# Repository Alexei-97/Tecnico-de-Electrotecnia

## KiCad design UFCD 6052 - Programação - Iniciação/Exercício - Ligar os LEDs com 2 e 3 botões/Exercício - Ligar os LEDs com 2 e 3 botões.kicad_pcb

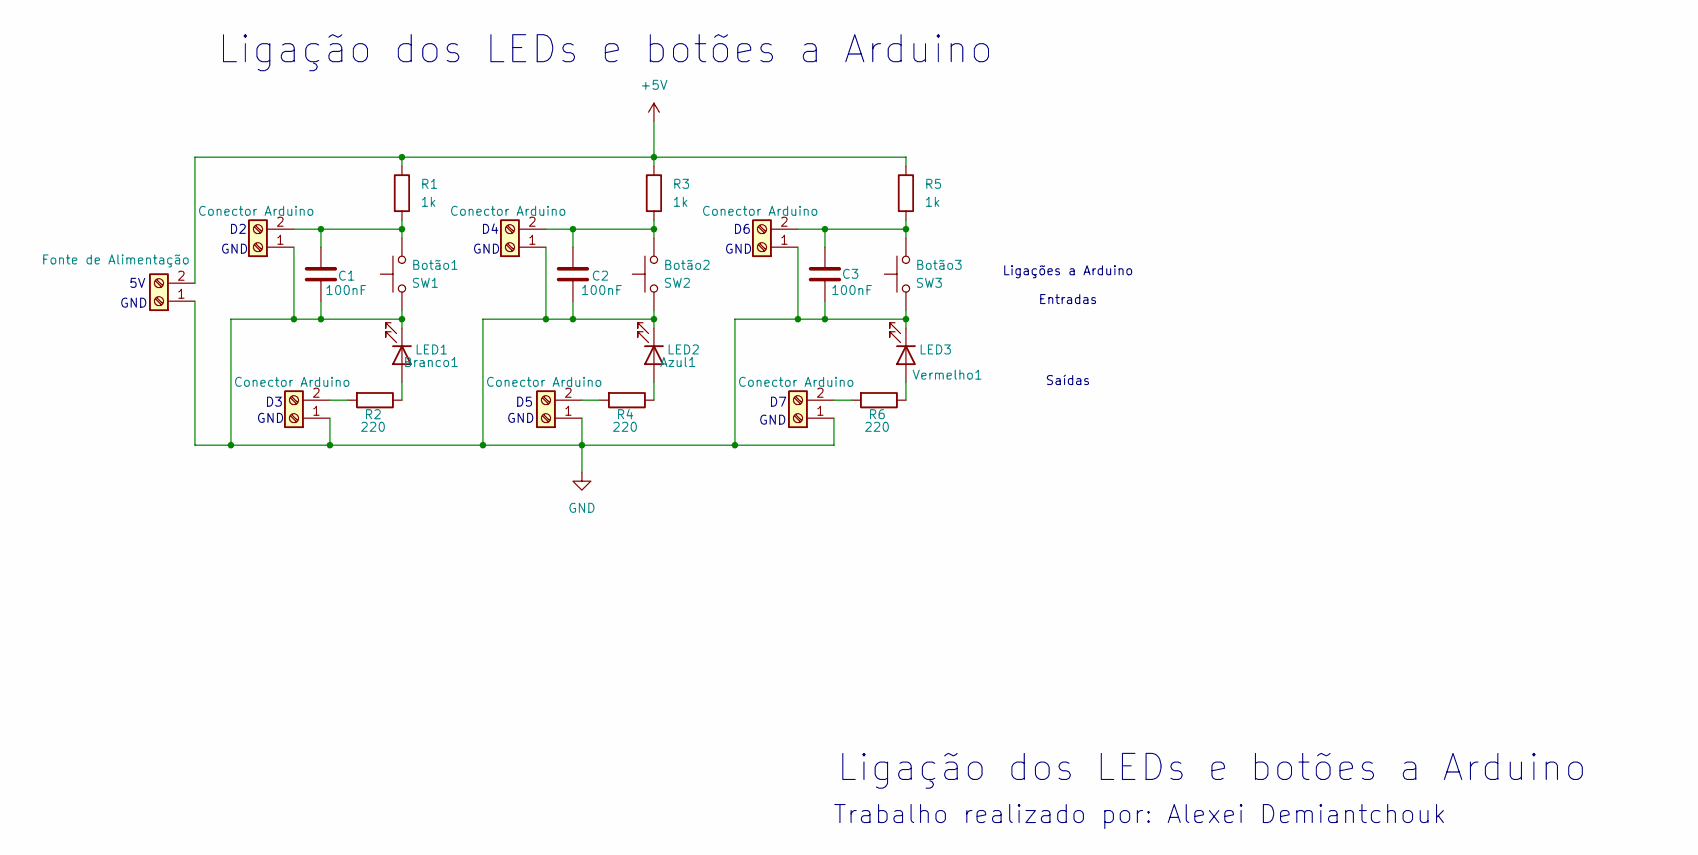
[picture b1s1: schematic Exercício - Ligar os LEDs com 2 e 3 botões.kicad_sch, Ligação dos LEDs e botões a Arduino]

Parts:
Azul1: LED2; LED_D5.0mm
Botão1: SW1; SW_PUSH_6mm_H7.3mm
Botão2: SW2; SW_PUSH_6mm_H7.3mm
Botão3: SW3; SW_PUSH_6mm_H7.3mm
Branco1: LED1; LED_D5.0mm
C1, C2, C3: 100nF; C_Disc_D5.0mm_W2.5mm_P5.00mm
J1, J2, J3, J4, J5, J6: Conector Arduino; TerminalBlock_MetzConnect_Type205_RT04502UBLC_1x02_P5.00mm_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
J7: Fonte de Alimentação; TerminalBlock_MetzConnect_Type205_RT04502UBLC_1x02_P5.00mm_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
R1, R3, R5: 1k; R_Axial_DIN0207_L6.3mm_D2.5mm_P10.16mm_Horizontal
R2, R4, R6: 220; R_Axial_DIN0207_L6.3mm_D2.5mm_P10.16mm_Horizontal
Vermelho1: LED3; LED_D5.0mm

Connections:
+5V: J7.2, R1.1, R3.1, R5.1
GND: Azul1.1 (K), Botão1.1, Botão2.1, Botão3.1, Branco1.1 (K), C1.2, C2.2, C3.2, J1.1, J2.1, J3.1, J4.1, J5.1, J6.1, J7.1, Vermelho1.1 (K)
unnamed: Azul1.2 (A), R4.1
unnamed: Branco1.2 (A), R2.1
unnamed: Botão1.2, C1.1, J1.2, R1.2
unnamed: Botão2.2, C2.1, J2.2, R3.2
unnamed: Botão3.2, C3.1, J3.2, R5.2
unnamed: J4.2, R2.2
unnamed: J5.2, R4.2
unnamed: J6.2, R6.2
unnamed: R6.1, Vermelho1.2 (A)

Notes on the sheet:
GND
Saídas
Ligação dos LEDs e botões a Arduino
Ligações a Arduino
Trabalho realizado por: Alexei Demiantchouk
Entradas

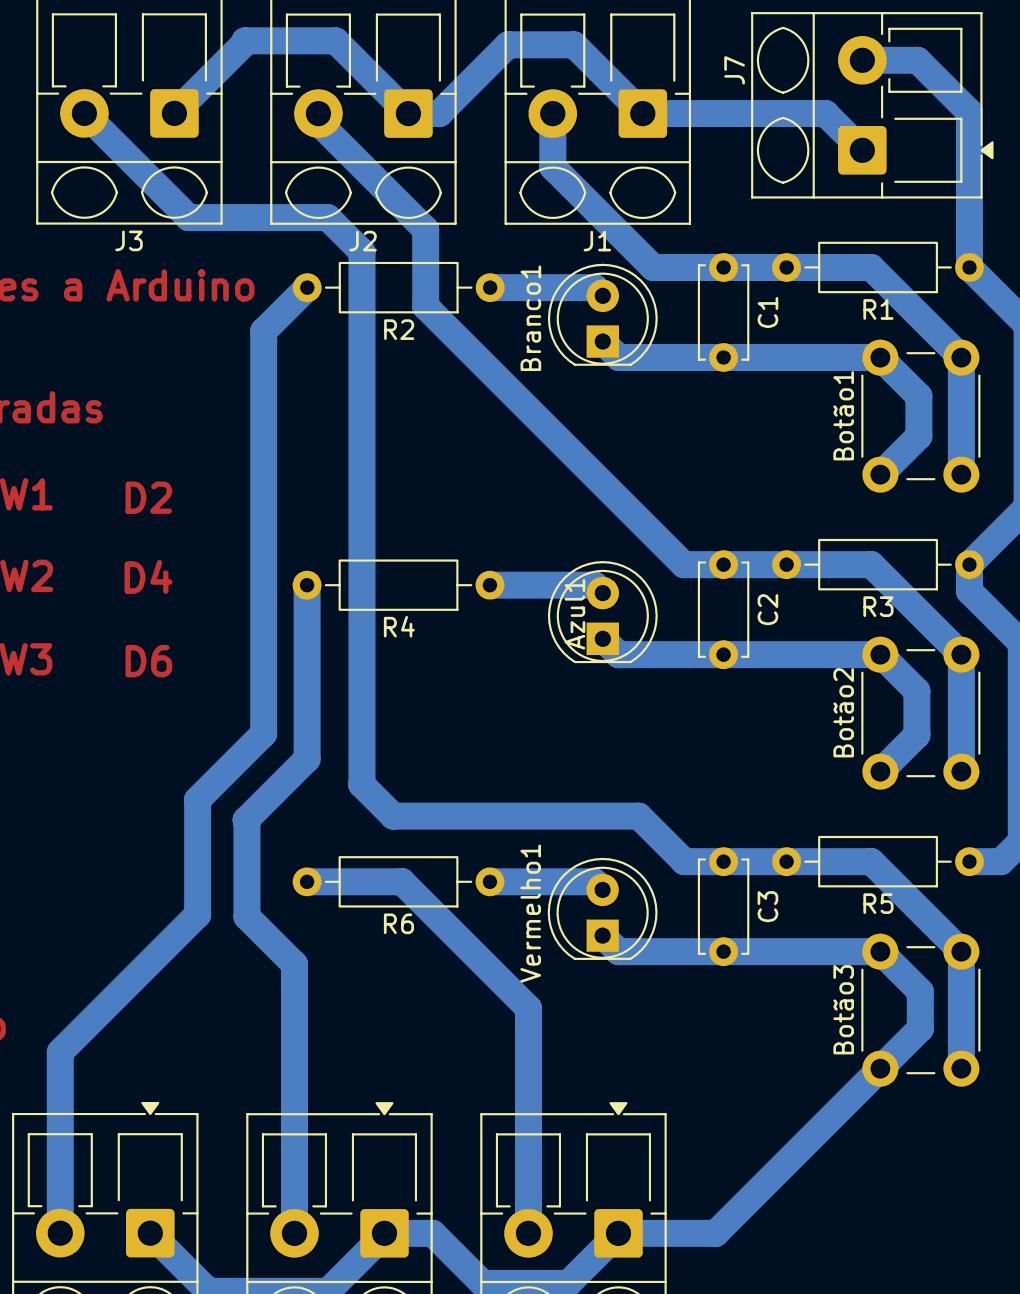
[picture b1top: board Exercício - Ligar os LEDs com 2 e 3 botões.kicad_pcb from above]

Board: 2 copper layers, 22 parts (0 on the bottom side), 11 nets.

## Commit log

2025-09-25 Adicionar pasta de 6051
2025-09-25 adicionar pasta 6052
